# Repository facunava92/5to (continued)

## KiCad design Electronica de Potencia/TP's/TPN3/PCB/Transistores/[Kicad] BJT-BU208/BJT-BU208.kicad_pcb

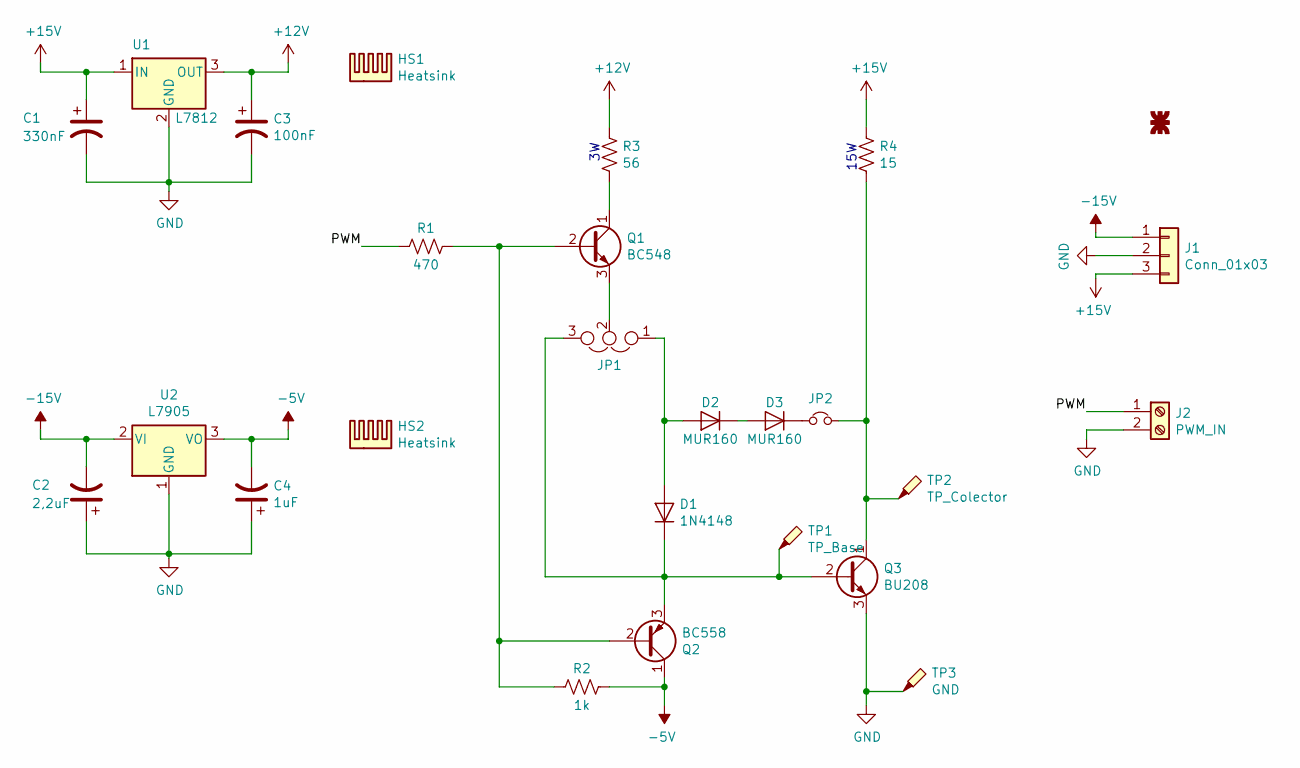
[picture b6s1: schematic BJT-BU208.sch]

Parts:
C1: 330nF; C_Disc_D4.7mm_W2.5mm_P5.00mm
C2: 2,2uF; C_Radial_D5.0mm_H11.0mm_P2.00mm
C3: 100nF; C_Disc_D5.0mm_W2.5mm_P2.50mm
C4: 1uF; C_Radial_D5.0mm_H11.0mm_P2.00mm
D1: 1N4148; D_DO-34_SOD68_P7.62mm_Horizontal
D2, D3: MUR160; D_DO-41_SOD81_P10.16mm_Horizontal
G1: logo; logo_utn_fsilk_small
HS1, HS2: Heatsink; Heatsink_TO220_A
J1: Conn_01x03; TerminalBlock_bornier-3_P5.08mm
J2: PWM_IN; TerminalBlock_bornier-2_P5.08mm
JP1: Jumper_NC_Dual; PinHeader_1x03_P2.54mm_Vertical
JP2: Jumper_NC_Small; PinHeader_1x02_P2.54mm_Vertical
Q1: BC548; TO-92_Inline
Q2: BC558; TO-92_Inline
Q3: BU208; TO-3
R1: 470; R_Axial_DIN0207_L6.3mm_D2.5mm_P10.16mm_Horizontal
R2: 1k; R_Axial_DIN0207_L6.3mm_D2.5mm_P10.16mm_Horizontal
R3: 56; R_Axial_DIN0516_L15.5mm_D5.0mm_P20.32mm_Horizontal
R4: 15; R_Axial_Power_L48.0mm_W12.5mm_P55.88mm
TP1: TP_Base; Testpoint
TP2: TP_Colector; Testpoint
TP3: GND; Testpoint
U1: L7812; TO-220-3_Vertical
U2: L7905; TO-220-3_Vertical

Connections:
+12V: C3.1, R3.1, U1.3 (OUT)
+15V: C1.1, J1.3, R4.1, U1.1 (IN)
-5V: C4.2, Q2.1 (C), R2.1, U2.3 (VO)
-15V: C2.2, J1.1, U2.2 (VI)
/PWM: J2.1, R1.2
GND: C1.2, C2.1, C3.2, C4.1, J1.2, J2.2, Q3.3 (E), TP3.1, U1.2 (GND), U2.1 (GND)
unnamed: D1.1 (K), JP1.3, Q2.3 (E), Q3.2 (B), TP1.1
unnamed: D1.2 (A), D2.2 (A), JP1.1
unnamed: D2.1 (K), D3.2 (A)
unnamed: D3.1 (K), JP2.1
unnamed: JP1.2, Q1.3 (E)
unnamed: JP2.2, Q3.1 (C), R4.2, TP2.1
unnamed: Q1.1 (C), R3.2
unnamed: Q1.2 (B), Q2.2 (B), R1.1, R2.2

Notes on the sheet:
15W

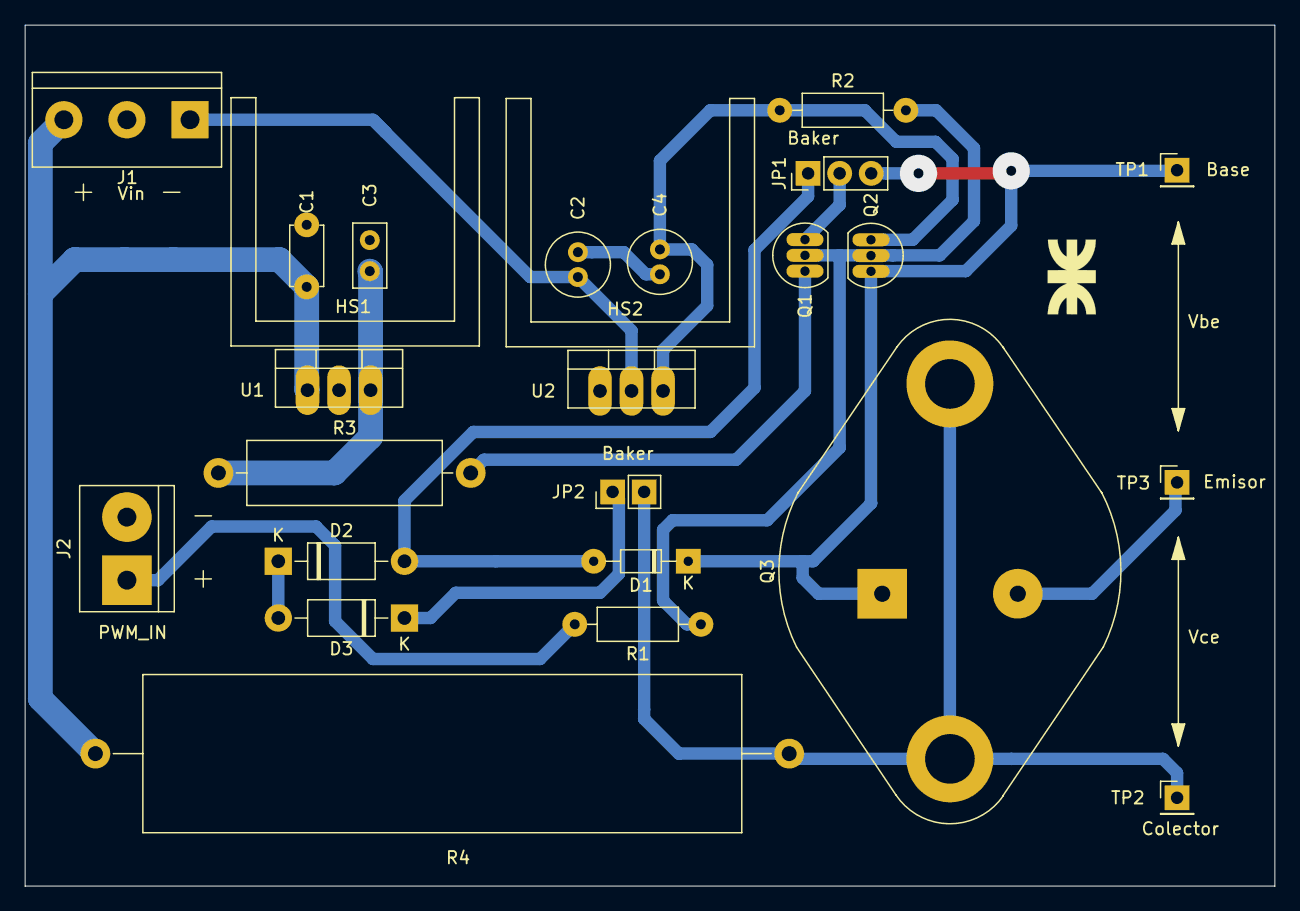
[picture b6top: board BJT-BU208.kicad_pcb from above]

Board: 2 copper layers, 100.7 x 69.3 mm, 26 parts (0 on the bottom side), 14 nets.

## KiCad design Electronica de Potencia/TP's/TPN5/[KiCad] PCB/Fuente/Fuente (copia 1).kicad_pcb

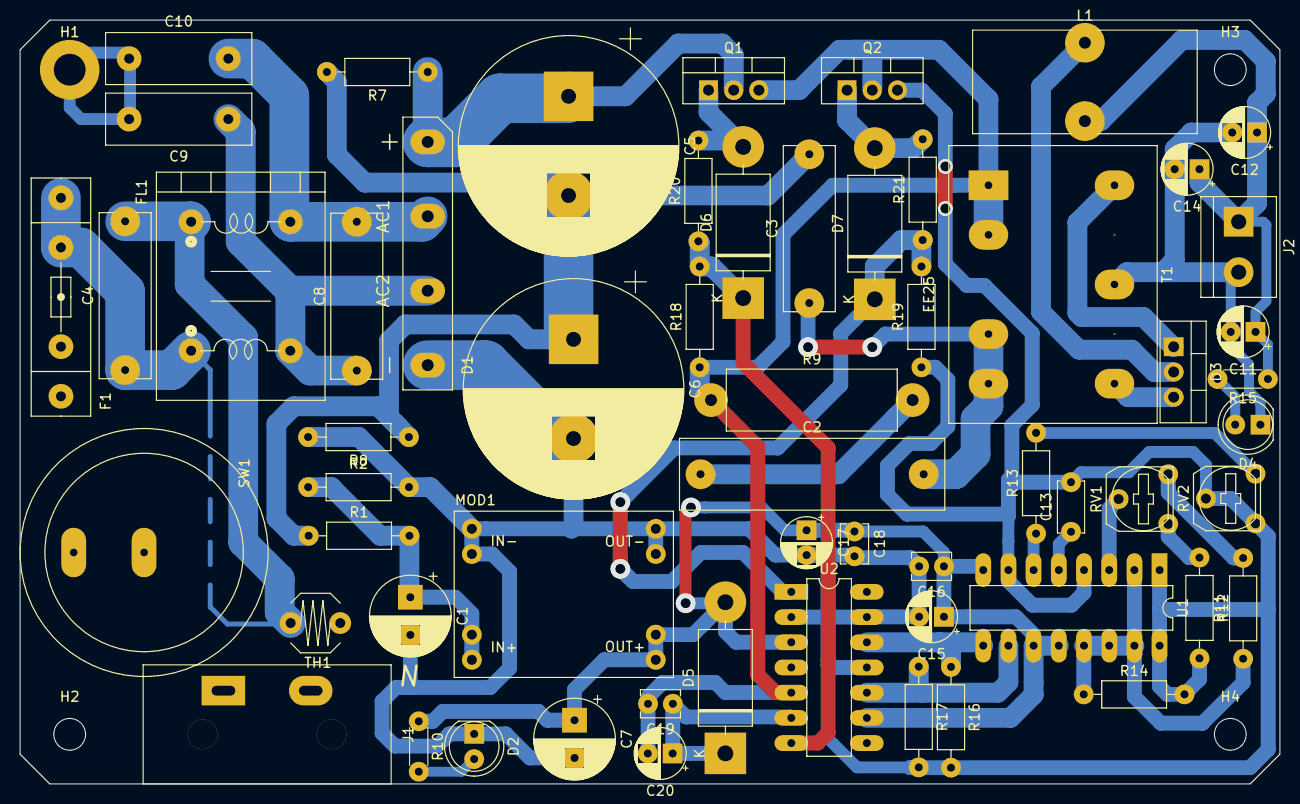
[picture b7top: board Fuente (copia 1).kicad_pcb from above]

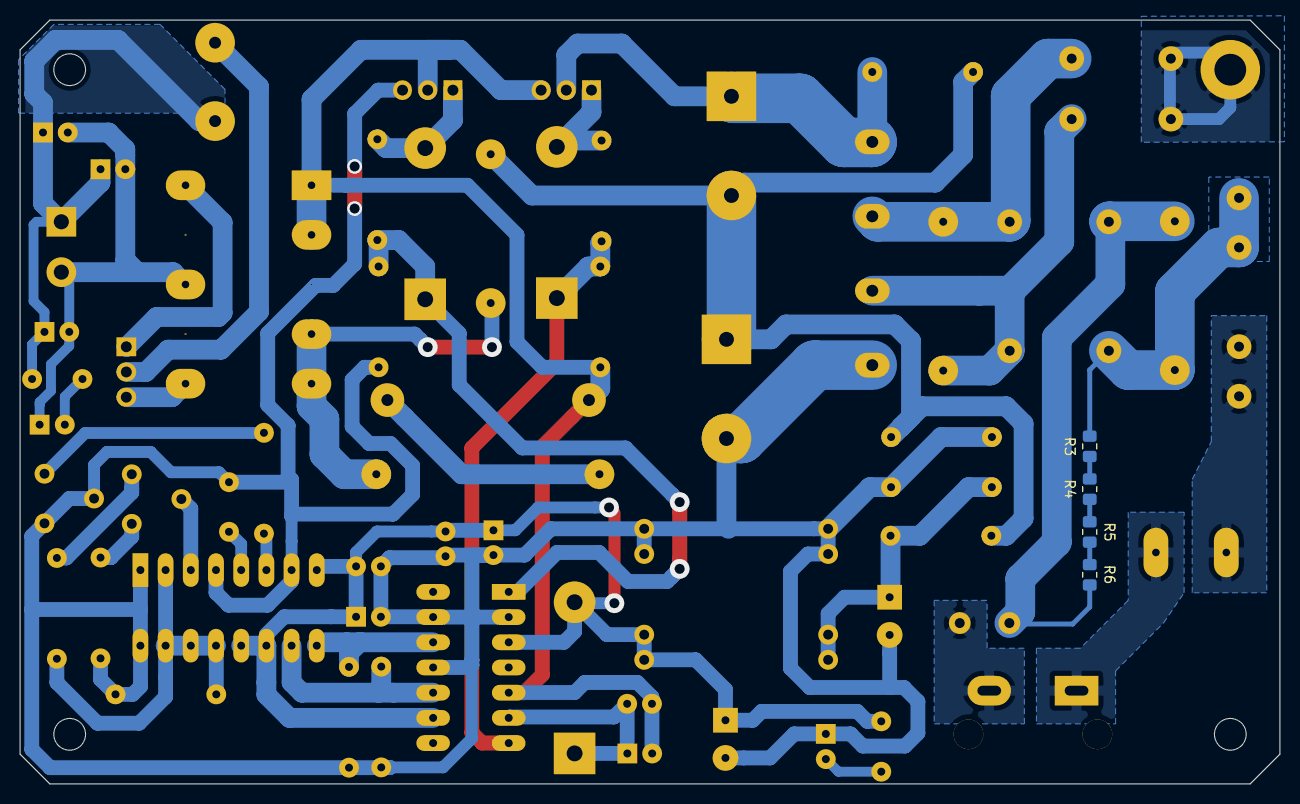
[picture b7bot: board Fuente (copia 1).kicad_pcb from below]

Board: 2 copper layers, 127.0 x 77.0 mm, 67 parts (4 on the bottom side), 40 nets.

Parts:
C1, C7: 330u|24V; CP_Radial_D8.0mm_P3.80mm
C2: 330nF|400V; C_Rect_L26.5mm_W7.0mm_P22.50mm_MKS4
C3, C4, C8: 0.1u; C_Rect_L16.5mm_W5.0mm_P15.00mm_MKT
C5, C6: 330u|200V; CP_Radial_D22.0mm_P10.00mm_SnapIn
C9, C10: 1n; C_EMI
C11, C12, C14: 10u|50V; CP_Radial_D5.0mm_P2.50mm
C13: 3,9n; C_Disc_D5.0mm_W2.5mm_P5.00mm
C15, C17: 10u; CP_Radial_D5.0mm_P2.50mm
C16, C18, C19: 0.1u; C_Disc_D3.8mm_W2.6mm_P2.50mm
C20: 4,7u; CP_Radial_D5.0mm_P2.50mm
D1: D3SB60; DS3B
D2: Verde_5mm; LED_D5.0mm_Clear
D3: MUR1660; TO-220-3_Vertical
D4: Amarillo_5mm; LED_D5.0mm_Clear
D5, D6, D7: MUR460; D_DO-201AD_P15.24mm_Horizontal
F1: 0,5 A; Fuse_4pin_A
FL1: Choke Coil; Choke_A
H1: MountingHole_Pad; MountingHole_3.2mm_M3_DIN965_Pad
H2, H3, H4: MountingHole; MountingHole_3.2mm_M3_DIN965
J1: 220 VAC; IEC-C8
J2: Salida +24V; TerminalBlock_bornier-2_P5.08mm
L1: INDUCTOR; L_Toroid_Vertical_L22.4mm_W10.2mm_P7.90mm_Vishay_TJ4
MOD1: MP1584
Q1, Q2: IRF840; TO-220-3_Vertical
R1: 6,8k; R_Axial_DIN0207_L6.3mm_D2.5mm_P10.16mm_Horizontal
R2, R14, R16, R17: 1K; R_Axial_DIN0207_L6.3mm_D2.5mm_P10.16mm_Horizontal
R3, R4, R5, R6: 20k; R_0805_2012Metric_Pad1.15x1.40mm_HandSolder
R7, R8: 100k; R_Axial_DIN0207_L6.3mm_D2.5mm_P10.16mm_Horizontal
R9: 56|3W; R_Axial_DIN0617_L17.0mm_D6.0mm_P20.32mm_Horizontal
R10: 2,2k; R_Axial_DIN0204_L3.6mm_D1.6mm_P5.08mm_Horizontal
R11: 2,2k; R_Axial_DIN0207_L6.3mm_D2.5mm_P10.16mm_Horizontal
R12: 10k; R_Axial_DIN0207_L6.3mm_D2.5mm_P10.16mm_Horizontal
R13: 1,5K; R_Axial_DIN0207_L6.3mm_D2.5mm_P10.16mm_Horizontal
R15: 10k; R_Axial_DIN0204_L3.6mm_D1.6mm_P5.08mm_Horizontal
R18, R19: 1k; R_Axial_DIN0207_L6.3mm_D2.5mm_P10.16mm_Horizontal
R20, R21: 22; R_Axial_DIN0207_L6.3mm_D2.5mm_P10.16mm_Horizontal
RV1: 5k; Trimpot_Horizontal
RV2: 1k; Trimpot_Horizontal
SW1: ROCKER; Rocker
T1: Transformer_1P_SS; Transformador_EE25
TH1: 16; NTC-16
U1: TL494; DIP-16_W7.62mm_LongPads
U2: IR2110; DIP-14_W7.62mm_LongPads

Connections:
+5V_REF: R11.1, R14.1, U1.2, U1.13, U1.14, U1.15
+15V: C7.1, C15.1, C16.1, C17.1, C18.1, D5.2, MOD1.3, R10.1, U1.8, U1.11, U1.12, U2.3, U2.9
F: C8.1, C9.1, D1.3, FL1.2
FB: RV1.2, U1.3
GNDPWR: C9.2, C10.1, H1.1
GNDREF: C11.2, C12.2, C14.2, D4.1, J2.2, T1.4
N: C8.2, C10.2, D1.2, FL1.4
unnamed: C1.1, MOD1.2, R1.2, R2.1
unnamed: C2.1, R9.2
unnamed: C2.2, C3.1, T1.2
unnamed: C4.1, F1.1, FL1.1, R3.1
unnamed: C4.2, FL1.3, R6.2, TH1.2
unnamed: C11.1, C12.1, C14.1, J2.1, L1.2, R15.1
unnamed: C13.1, U1.5
unnamed: C19.1, C20.1, D5.1, U2.6
unnamed: D2.2, R10.2
unnamed: D3.1, T1.5
unnamed: D3.2, L1.1
unnamed: D3.3, T1.3
unnamed: D4.2, R15.2
unnamed: D6.1, R18.2, R20.1, U2.7
unnamed: D7.1, R19.2, R21.1, U2.1
unnamed: F1.2, SW1.2
unnamed: J1.1, SW1.1
unnamed: J1.2, TH1.1
unnamed: R3.2, R4.1
unnamed: R4.2, R5.1
unnamed: R5.2, R6.1
unnamed: R11.2, RV1.1
unnamed: R12.1, RV1.3
unnamed: R13.1, U1.6
unnamed: R13.2, RV2.1
PWM_A: R16.1, U1.9, U2.12
PWM_B: R17.1, U1.10, U2.10
VG1: D6.2, Q1.1, R20.2
VG2: D7.2, Q2.1, R21.2
VS1: C19.2, C20.2, Q1.3, Q2.2, R9.1, R18.1, T1.1, U2.5
VS2: C1.2, C6.2, C7.2, C13.2, C15.2, C16.2, C17.2, C18.2, D1.4, D2.1, MOD1.1, MOD1.4, Q2.3, R2.2, R8.2, R12.2, R14.2, R16.2, R17.2, R19.1, RV2.2, RV2.3, U1.1, U1.4, U1.7, U1.16, U2.2, U2.11, U2.13
Vin: C5.1, D1.1, Q1.2, R7.1
Vin|2: C3.2, C5.2, C6.1, R1.1, R7.2, R8.1

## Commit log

2019-04-01 Agrego carpeta TD3
2019-04-01 Agrego 8, no se por que no une el LED con la salida del comparador
2019-04-02 primer commit desde matimasdiez
2019-04-02 segundo commit desde matimasdiez
2019-04-02 tercer commit desde matimasdiez
2019-04-02 Arregle el 8 de TD3, no estoy seguro de que ande bien el LED, pero esta para visar
2019-04-02 añadi el oscilador1 hecho en genesys
2019-04-04 Ordeno a little bit
2019-04-05 agrego el multisim de potencia tp1
2019-04-06 subo oscilador
2019-04-06 oscilsdor qucs
2019-04-06 osc qucs
2019-04-06 Organizo a little more, agrego lo de tecnicas guia tp2
2019-04-06 Agrego regimen de promocion Aplicada3
2019-04-06 Agrego Calendario de Practicos Aplicada3
2019-04-06 Cambio condiciones de promo
2019-04-11 Agrego cosillas
2019-04-13 organizo carpetas, agrego hasta tp2 de tecnicas guia 2
2019-04-13 Lamas puso diapositiva en blanco
2019-04-13 subo pcb clapp en altium
2019-04-14 Organizo a little bit
2019-04-15 Agrego PCB de potencia
2019-04-15 Modularizo el proyecto para que sea portable para cualquiera, completo 3d's, me falta conseguir la Res de 5W para ver si corresponde el fp
2019-04-16 Arreglo footprint de UJT
2019-04-16 Arreglando a little bit
2019-04-16 panelizo dimmer
2019-04-17 progreso en el informe del TP2 y agrego capturas del TP1 de potencia
2019-04-17 Informe TP2 potencia casi completo, falta fotos de mediciones y contrastar la alinealidad
2019-04-21 Agrego carpeta de tecnologia
2019-04-22 Agrego cosas de tecnologia
2019-04-23 Arreglo cosillas de potencia
2019-04-23 Rediseño dimmer
2019-04-27 algo en el dimmer
2019-05-02 TP2 de aplicada casi terminado, voy a cambiar algo de la conclusion, pero lo grueso queda tal cual
2019-05-03 Agrego TP1 Potencia
2019-05-05 Actualizo desde ASUS
2019-05-08 [EA3] Hartley en AWR
2019-05-09 clapp fecha 9mayo
2019-05-09 clapp 9mayo
2019-05-10 Agrego rediseño de Hartley (kicad)
2019-05-10 Agrego PCB de PWM, TP3 de aplicada
2019-05-11 Se agrega guia 2 de tecnicas y enunciado de guia 3
2019-05-13 clapp que anda del año pasado 1
2019-05-13 simulaciones clapp
2019-05-13 Actualizo repo
2019-05-14 Avanzo el tp3 de potencia
2019-05-16 Agrego simulaciones de TP1 de Aplicada, Agrego nota de coloquio de potencia
2019-05-16 para el chingueguencha de Berti de todo cariño tus amigos 5to
2019-05-16 Actualizo con placa 2 de potencia
2019-05-20 Placa TP3 transistor completa
2019-05-21 Termino placa 3 de potencia
2019-05-21 Actualizo placa MOSFET_IGBT de potencia
2019-05-21 Organizo un poco, panelizo placas de transistores potencia TP3
2019-05-21 Agrego fotos de placas
2019-05-22 Agrego guia de ejercicios de aplicada3
2019-05-25 Subo TP2 corregido
2019-05-25 Arreglo un toque el TP2 de potencia
2019-05-27 elimino carpeta de tecno
2019-05-27 Agrego Informe de TP3 de aplicada
2019-05-28 mezcladores
2019-05-29 Actualizo
2019-05-30 actualizashion
2019-06-02 Arreglo placa de potencia
2019-06-04 Arreglo placa BJT potencia
2019-06-04 Agrego un poco de to
2019-06-06 actualizaishion
2019-06-06 Agrego informe de medidas2
2019-06-07 agrego lena
2019-06-07 agrego td3 practico guia 3
2019-06-09 Agrego TP3 visado de tecnicas
2019-06-09 [TD3] Agrego el tp3 revisado y enviado
2019-06-11 Agrego TP1 de Aplicada
2019-06-12 prueba
2019-06-12 desde ASUS
2019-06-12 prueba2
2019-06-14 desde asus agrego simulaciones del TP3
2019-06-14 agrego PLL
2019-06-14 asdasd
2019-06-16 arreglo error PLL y actualizo valores
2019-06-16 agrego desde asus
2019-06-17 Agrego TP3 casi completo, falta conclusion
2019-06-18 termino TP3 de aplicada
2019-06-21 modifico mezcladores segun guia mombay, tiene mas sentido
2019-06-25 actualizo informe aplicada, me olvide de cambiar el circuito del balanceo doble
2019-07-01 actualzio
2019-07-15 Agrego TP4 de potencia e informes de TP5 potencia
2019-07-24 TP4 PLL
2019-07-24 cambio de PC
2019-07-25 actualizo TP3 con Figura de ruido
2019-08-02 TP4 de Tecnicas
2019-08-03 corregido
2019-08-03 agregue corregido 3
2019-08-03 empiezo TP4 de tecnicas
2019-08-04 ejercicio 6 y 7
2019-08-04 lamas 6 y 7
2019-08-08 LabView 2013
2019-08-20 Subo progreso de fuente
2019-08-20 Corrigo TP4 de TD3
2019-08-23 actualizo fuente
2019-08-24 Agrego TP5 de tecnicas, hecho hasta el 2 inclusive
2019-08-28 Agrego hasta TP4 de tecnicas y funcion seno.m
2019-08-29 TP5 tecnicas
2019-08-30 Actualizo todo TP5 de tecnicas
2019-08-30 actualizo TP td3
2019-09-14 TP7 potencia
2019-09-28 Llave H
2019-10-05 Cambio el PCB de la fuente
2019-10-19 medidas 2 informe
2019-10-23 informe
2019-10-24 actualizo desde envy
2019-10-24 informe medidas
2019-10-24 Agrego TP final de Lamas de Medidas, TP6 y empiezo TP7 de tecnicas
2019-10-25 Agrego td3
2019-10-25 Agrego TP final medidas
2019-10-26 actualizo TP medidas
2019-10-28 Actualizo el tp d medidas
2019-10-29 Agrego TP4 de td3
2019-10-31 Agrego TP5 de td3
2019-11-02 Agrego TP7 enviado a Paredes
2019-11-02 Agrego TP5 Potencia
2019-11-08 Agrego desde Envy
2019-11-09 Agrego TP7 potencia
2019-11-11 Agrego simulaciones TP6 Aplicada
2019-11-11 Agrego tecno
2019-11-11 Agrego TP1 tecnologia completo
2019-11-11 Arreglo moco
2019-11-13 Agrego paper
2019-11-15 Ordeno
2019-11-24 Agrego TP7 Aplicada
2019-12-22 Agrego TP8 y TP9 de potencia
2019-12-22 Completo Medidas
2019-12-26 Corrijo Paper
2020-03-07 Agrego TP9
